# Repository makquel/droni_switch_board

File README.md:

# droni_switch_board
Proprietary hardware commutation board (manual/automatic pilot) for autonomous airship (DRONI)

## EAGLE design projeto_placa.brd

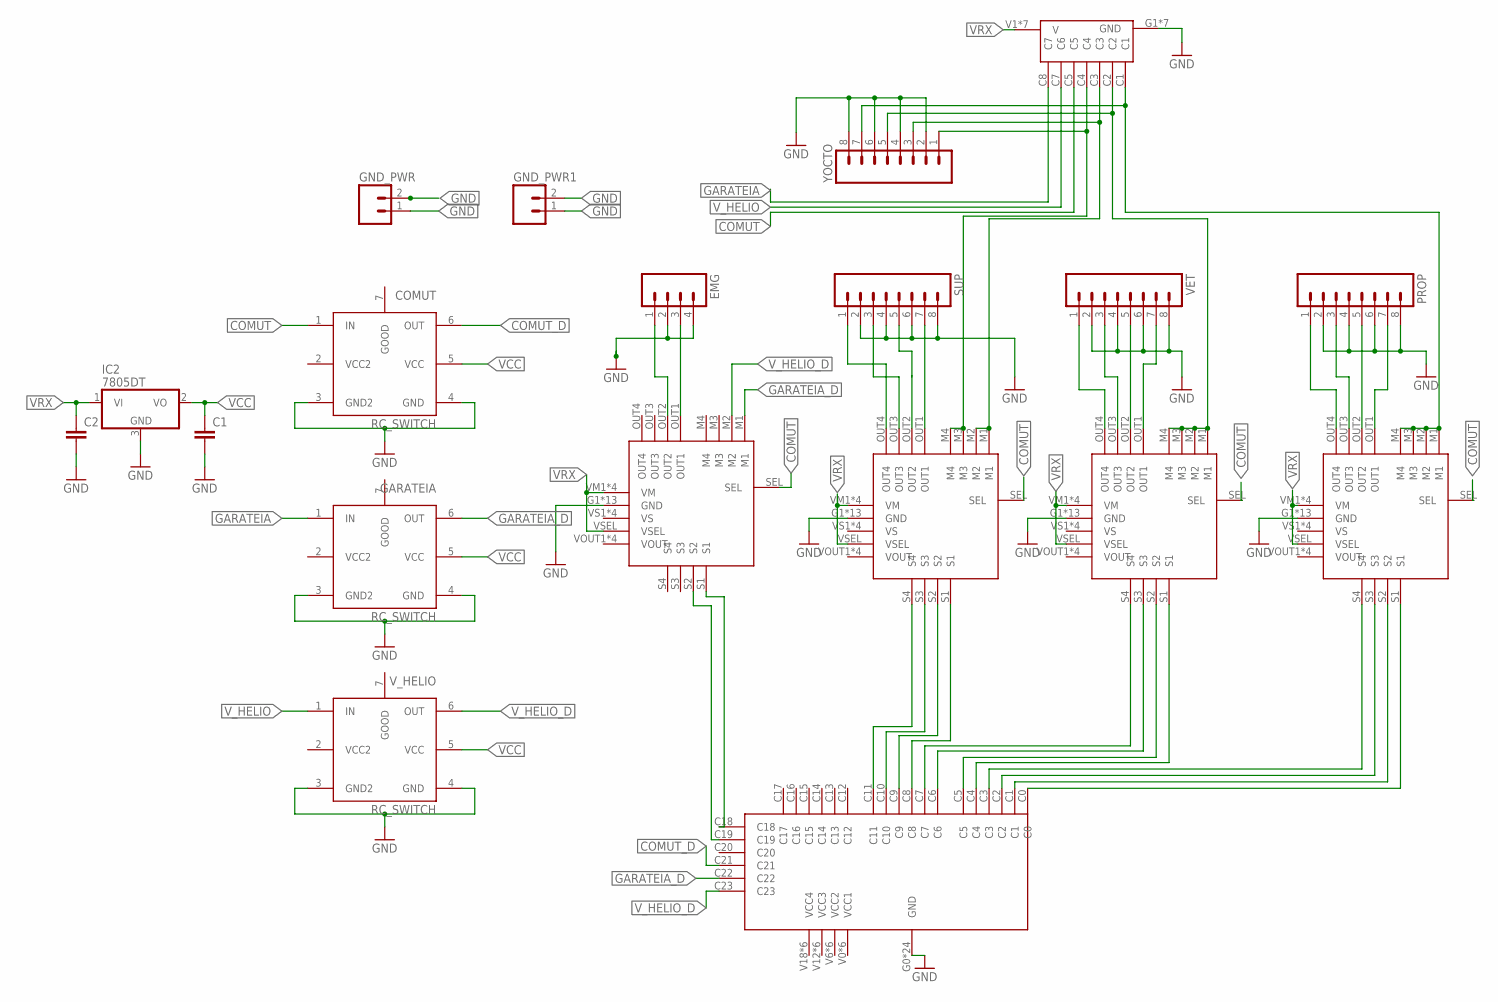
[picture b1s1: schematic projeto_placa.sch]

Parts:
C1, C2: C-EUC0805; C0805
COMUT: RC_SWITCH; 7PINS_POLOLU
EMG: M04PTH; 1X04
GARATEIA: RC_SWITCH; 7PINS_POLOLU
GND_PWR, GND_PWR1: M025MM; SCREWTERMINAL-5MM-2
IC2: 7805DT; TO252
PROP: M08; 1X08_ROUND
RX_IN: RX_IN
SUP: M08; 1X08_ROUND
U$1: POLOLU_MAESTRO_24CH; POLOLU_MAESTRO_24
U$3, U$4, U$5, U$6: POLOLU_MUX_4CH; POLOLU_MUX
VET: M08; 1X08_ROUND
V_HELIO: RC_SWITCH; 7PINS_POLOLU
YOCTO: M08SILK_FEMALE_PTH; 1X08

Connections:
COMUT: COMUT.1 (IN), RX_IN.C5, U$3.SEL, U$4.SEL, U$5.SEL, U$6.SEL
COMUT_D: COMUT.6 (OUT), U$1.C21
GARATEIA: GARATEIA.1 (IN), RX_IN.C8 (C7)
GARATEIA_D: GARATEIA.6 (OUT), U$1.C22, U$6.M1
GND: C1.2, C2.2, COMUT.3 (GND2), COMUT.4 (GND), EMG.2, EMG.4, GARATEIA.3 (GND2), GARATEIA.4 (GND), GND_PWR.1, GND_PWR.2, GND_PWR1.1, GND_PWR1.2, IC2.3 (GND), PROP.2, PROP.4, PROP.6, PROP.8, RX_IN.G1 (GND), RX_IN.G2 (GND), RX_IN.G3 (GND), RX_IN.G4 (GND), RX_IN.G5 (GND), RX_IN.G6 (GND), RX_IN.G7 (GND), SUP.2, SUP.4, SUP.6, SUP.8, U$1.G0 (GND), U$1.G1 (GND), U$1.G2 (GND), U$1.G3 (GND), U$1.G4 (GND), U$1.G5 (GND), U$1.G6 (GND), U$1.G7 (GND), U$1.G8 (GND), U$1.G9 (GND), U$1.G10 (GND), U$1.G11 (GND), U$1.G12 (GND), U$1.G13 (GND), U$1.G14 (GND), U$1.G15 (GND), U$1.G16 (GND), U$1.G17 (GND), U$1.G18 (GND), U$1.G19 (GND), U$1.G20 (GND), U$1.G21 (GND), U$1.G22 (GND), U$1.G23 (GND), U$3.G1 (GND), U$3.G2 (GND), U$3.G3 (GND), U$3.G4 (GND), U$3.G5 (GND), U$3.G6 (GND), U$3.G7 (GND), U$3.G8 (GND), U$3.G9 (GND), U$3.G10 (GND), U$3.G11 (GND), U$3.G12 (GND), U$3.G13 (GND), U$4.G1 (GND), U$4.G2 (GND), U$4.G3 (GND), U$4.G4 (GND), U$4.G5 (GND), U$4.G6 (GND), U$4.G7 (GND), U$4.G8 (GND), U$4.G9 (GND), U$4.G10 (GND), U$4.G11 (GND), U$4.G12 (GND), U$4.G13 (GND), U$5.G1 (GND), U$5.G2 (GND), U$5.G3 (GND), U$5.G4 (GND), U$5.G5 (GND), U$5.G6 (GND), U$5.G7 (GND), U$5.G8 (GND), U$5.G9 (GND), U$5.G10 (GND), U$5.G11 (GND), U$5.G12 (GND), U$5.G13 (GND), U$6.G1 (GND), U$6.G2 (GND), U$6.G3 (GND), U$6.G4 (GND), U$6.G5 (GND), U$6.G6 (GND), U$6.G7 (GND), U$6.G8 (GND), U$6.G9 (GND), U$6.G10 (GND), U$6.G11 (GND), U$6.G12 (GND), U$6.G13 (GND), VET.2, VET.4, VET.6, VET.8, V_HELIO.3 (GND2), V_HELIO.4 (GND), YOCTO.2, YOCTO.4, YOCTO.6, YOCTO.8
unnamed: U$1.C0, U$5.S1
unnamed: PROP.5, U$5.OUT2
unnamed: U$1.C1, U$5.S2
unnamed: U$1.C2, U$5.S3
unnamed: U$1.C3, U$5.S4
unnamed: U$1.C4, U$4.S1
unnamed: U$1.C5, U$4.S2
unnamed: U$1.C6, U$4.S3
unnamed: U$1.C7, U$4.S4
unnamed: U$1.C8, U$3.S1
unnamed: U$1.C9, U$3.S2
unnamed: U$1.C10, U$3.S3
unnamed: U$1.C11, U$3.S4
unnamed: U$1.C18, U$6.S1
unnamed: U$1.C19, U$6.S2
unnamed: EMG.3, U$6.OUT1
unnamed: PROP.7, U$5.OUT1
unnamed: PROP.3, U$5.OUT3
unnamed: PROP.1, U$5.OUT4
unnamed: U$4.OUT1, VET.7
unnamed: U$4.OUT2, VET.5
unnamed: U$4.OUT3, VET.3
unnamed: U$4.OUT4, VET.1
unnamed: SUP.7, U$3.OUT1
unnamed: SUP.5, U$3.OUT2
unnamed: SUP.3, U$3.OUT3
unnamed: SUP.1, U$3.OUT4
unnamed: RX_IN.C1, U$5.M1, U$5.M2, U$5.M3, U$5.M4, YOCTO.7
unnamed: RX_IN.C2, U$4.M1, U$4.M2, U$4.M3, U$4.M4, YOCTO.5
unnamed: RX_IN.C4, U$3.M3, U$3.M4, YOCTO.1
unnamed: EMG.1, U$6.OUT2
unnamed: RX_IN.C3, U$3.M1, U$3.M2, YOCTO.3
VCC: C1.1, COMUT.5 (VCC), GARATEIA.5 (VCC), IC2.2 (VO), V_HELIO.5 (VCC)
VRX: C2.1, IC2.1 (VI), RX_IN.V1 (V), RX_IN.V2 (V), RX_IN.V3 (V), RX_IN.V4 (V), RX_IN.V5 (V), RX_IN.V6 (V), RX_IN.V7 (V), U$3.VM1 (VM), U$3.VM2 (VM), U$3.VM3 (VM), U$3.VM4 (VM), U$3.VSEL, U$4.VM1 (VM), U$4.VM2 (VM), U$4.VM3 (VM), U$4.VM4 (VM), U$4.VSEL, U$5.VM1 (VM), U$5.VM2 (VM), U$5.VM3 (VM), U$5.VM4 (VM), U$5.VSEL, U$6.VM1 (VM), U$6.VM2 (VM), U$6.VM3 (VM), U$6.VM4 (VM), U$6.VSEL
V_HELIO: RX_IN.C7 (C6), V_HELIO.1 (IN)
V_HELIO_D: U$1.C23, U$6.M2, V_HELIO.6 (OUT)

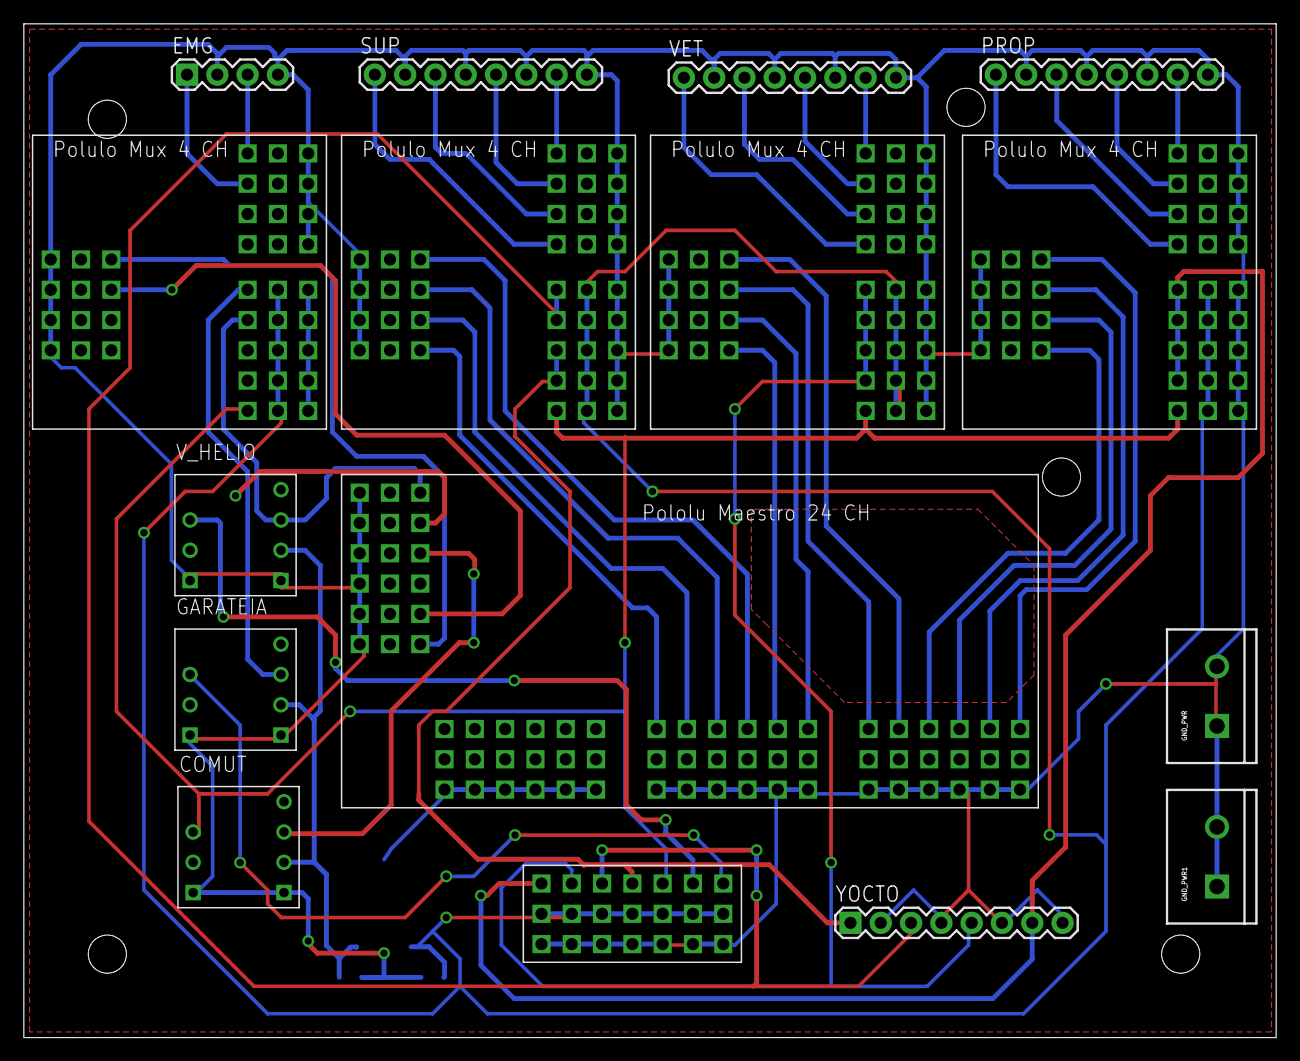
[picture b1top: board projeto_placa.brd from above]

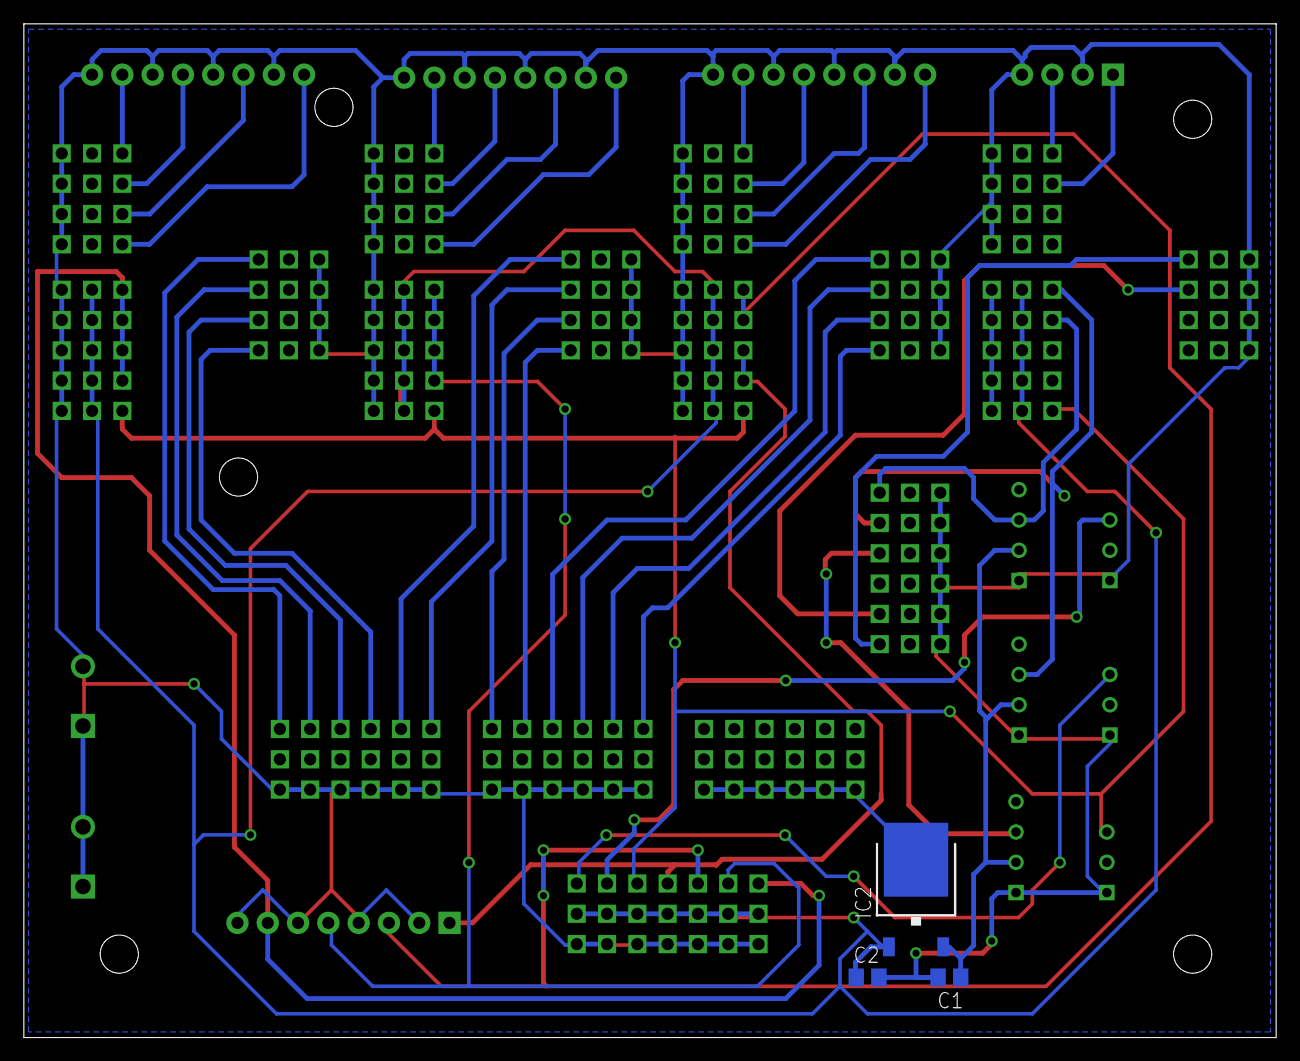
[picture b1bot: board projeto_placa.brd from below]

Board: 2 copper layers, 105.0 x 85.0 mm, 19 parts (3 on the bottom side), 41 nets.

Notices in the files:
parts and their libraries:
SparkFun-Connectors: Licensing: Creative Commons ShareAlike 4.0 International - https://creativecommons.org/licenses/by-sa/4.0
